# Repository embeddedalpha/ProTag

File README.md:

# ProTag  

### Schematic:

### 1

### 2

### 3

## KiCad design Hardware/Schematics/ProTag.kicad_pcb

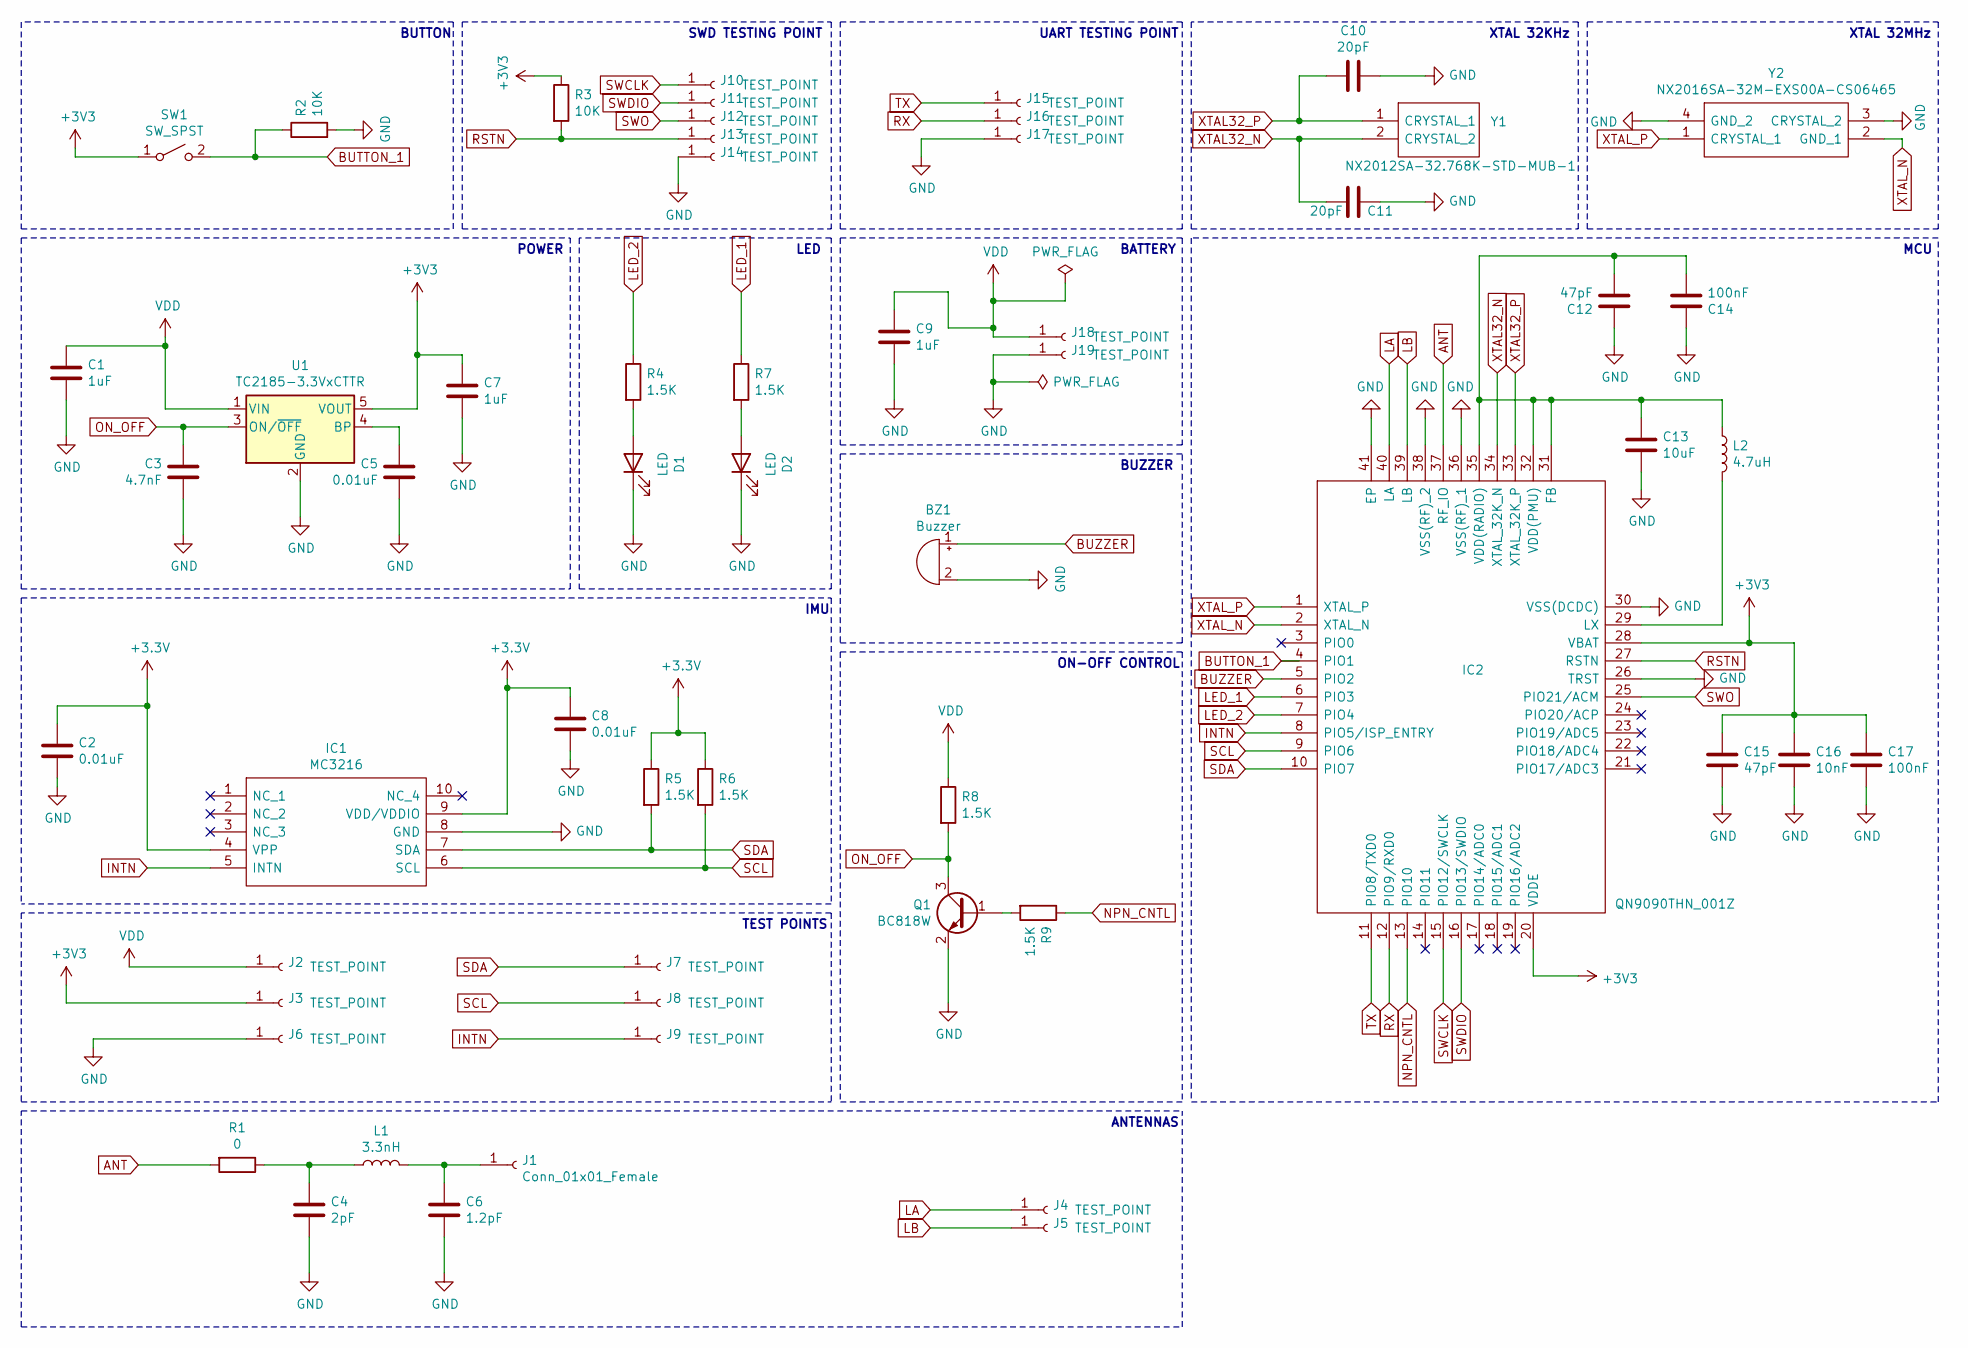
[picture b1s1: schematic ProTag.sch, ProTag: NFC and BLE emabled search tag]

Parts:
BZ1: Buzzer
C1, C7, C9: 1uF; C_0402_1005Metric
C2, C5, C8: 0.01uF; C_0201_0603Metric
C3: 4.7nF; C_0201_0603Metric
C4: 2pF; C_0201_0603Metric
C6: 1.2pF; C_0201_0603Metric
C10, C11: 20pF; C_0201_0603Metric
C12, C15: 47pF; C_0201_0603Metric
C13: 10uF; C_0201_0603Metric
C14, C17: 100nF; C_0201_0603Metric
C16: 10nF; C_0201_0603Metric
D1, D2: LED; D_0201_0603Metric
IC1: MC3216; SON50P300X300X100-10N; Mouser Part Number 498-MC3216
IC2: QN9090THN_001Z; QFN50P600X600X100-41N-D; Mouser Part Number 771-QN9090THN/001Z
J1: Conn_01x01_Female; TestPoint_Pad_D1.0mm
J2, J3, J4, J5, J6, J7, J8, J9, J10, J11, J12, J13, J14, J15, J16, J17, J18, J19: TEST_POINT; TestPoint_Pad_D1.0mm
L1: 3.3nH; L_0201_0603Metric
L2: 4.7uH; L_0201_0603Metric
Q1: BC818W; SOT-323_SC-70
R1: 0; R_0201_0603Metric
R2, R3: 10K; R_0201_0603Metric
R4, R5, R6, R7, R8, R9: 1.5K; R_0201_0603Metric
SW1: SW_SPST; SW_SPST_TL3342
U1: TC2185-3.3VxCTTR; SOT-23-5
Y1: NX2012SA-32.768K-STD-MUB-1; NX2012SA32768KSTDMUB1; Mouser Part Number 344-NX2012SA32768K1
Y2: NX2016SA-32M-EXS00A-CS06465; NX2016SA32MEXS00ACS06465; Mouser Part Number 344-NX2016SA32S06465

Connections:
ANT: IC2.37 (RF_IO), R1.2
BUTTON_1: IC2.4 (PIO1), R2.1, SW1.2 (B)
BUZZER: BZ1.1 (-), IC2.5 (PIO2)
GND: BZ1.2 (+), C1.1, C2.1, C3.1, C4.2, C5.1, C6.2, C7.1, C8.1, C9.1, C10.1, C11.2, C12.2, C13.2, C14.2, C15.2, C16.1, C17.2, D1.1 (K), D2.1 (K), IC1.8 (GND), IC2.26 (TRST), IC2.30 (VSS(DCDC)), IC2.36 (VSS(RF)_1), IC2.38 (VSS(RF)_2), IC2.41 (EP), J6.1, J14.1, J17.1, J19.1, Q1.2 (E), R2.2, U1.2 (GND), Y2.3 (CRYSTAL_2), Y2.4 (GND_2)
INTN: IC1.5 (INTN), IC2.8 (PIO5/ISP_ENTRY), J9.1
LA: IC2.40 (LA), J4.1
LB: IC2.39 (LB), J5.1
LED_1: IC2.6 (PIO3), R7.1
LED_2: IC2.7 (PIO4), R4.1
NPN_CNTL: IC2.13 (PIO10), R9.1
unnamed: C4.1, L1.1, R1.1
unnamed: C5.2, U1.4 (BP)
unnamed: C6.1, J1.1, L1.2
unnamed: C12.1, C13.1, C14.1, IC2.31 (FB), IC2.32 (VDD(PMU)), IC2.35 (VDD(RADIO)), L2.1
unnamed: D1.2 (A), R4.2
unnamed: D2.2 (A), R7.2
unnamed: IC2.29 (LX), L2.2
unnamed: Q1.1 (B), R9.2
ON_OFF: C3.2, Q1.3 (C), R8.2, U1.3 (ON/~OFF~)
RSTN: IC2.27 (RSTN), J13.1, R3.2
RX: IC2.12 (PIO9/RXD0), J16.1
SCL: IC1.6 (SCL), IC2.9 (PIO6), J8.1, R6.2
SDA: IC1.7 (SDA), IC2.10 (PIO7), J7.1, R5.2
SWCLK: IC2.15 (PIO12/SWCLK), J10.1
SWDIO: IC2.16 (PIO13/SWDIO), J11.1
SWO: IC2.25 (PIO21/ACM), J12.1
TX: IC2.11 (PIO8/TXD0), J15.1
VDD: C1.2, C9.2, J2.1, J18.1, R8.1, U1.1 (VIN)
XTAL32_N: C11.1, IC2.34 (XTAL_32K_N), Y1.2 (CRYSTAL_2)
XTAL32_P: C10.2, IC2.33 (XTAL_32K_P), Y1.1 (CRYSTAL_1)
XTAL_N: IC2.2 (XTAL_N), Y2.2 (GND_1)
XTAL_P: IC2.1 (XTAL_P), Y2.1 (CRYSTAL_1)

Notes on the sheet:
MCU
XTAL 32MHz
XTAL 32KHz
UART TESTING POINT
SWD TESTING POINT
BUTTON
ANTENNAS
POWER
BATTERY
LED
IMU
BUZZER
TEST POINTS
ON-OFF CONTROL

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
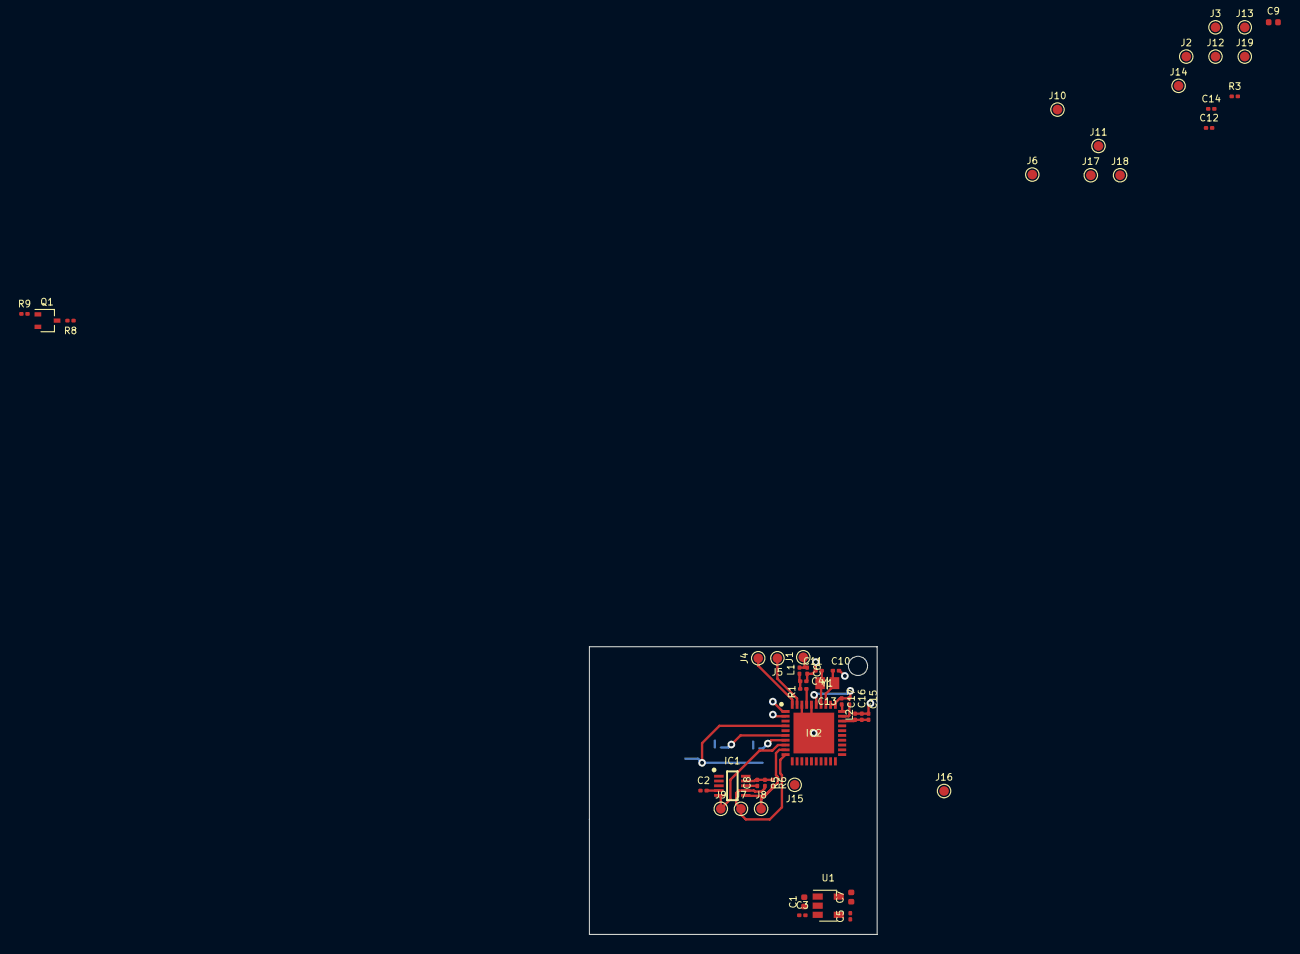
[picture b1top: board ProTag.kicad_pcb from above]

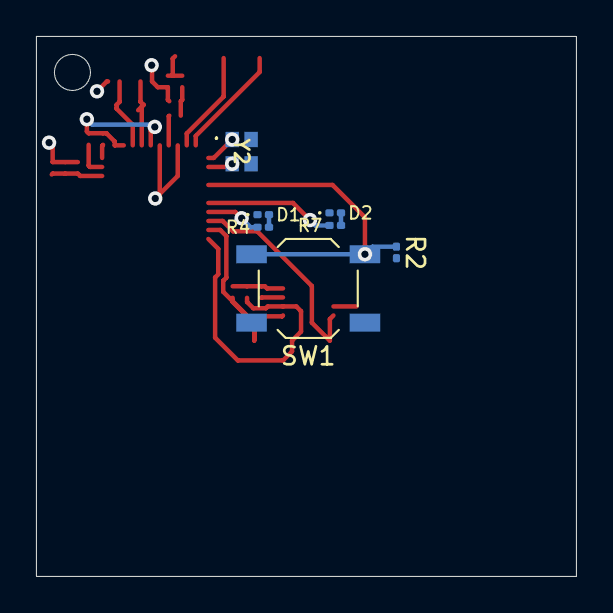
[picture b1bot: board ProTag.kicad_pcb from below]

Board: 2 copper layers, 30.0 x 30.0 mm, 56 parts (7 on the bottom side), 32 nets.

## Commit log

2021-05-05 Create txt
